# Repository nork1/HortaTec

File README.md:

# HortaTec

Ficheiros com o código utilizado no microcontrolador ESP32-S2, tal como um backup do sistema Home Assistant e os ficheiros do desenvolvimento do PCB no Autodesk EAGLE

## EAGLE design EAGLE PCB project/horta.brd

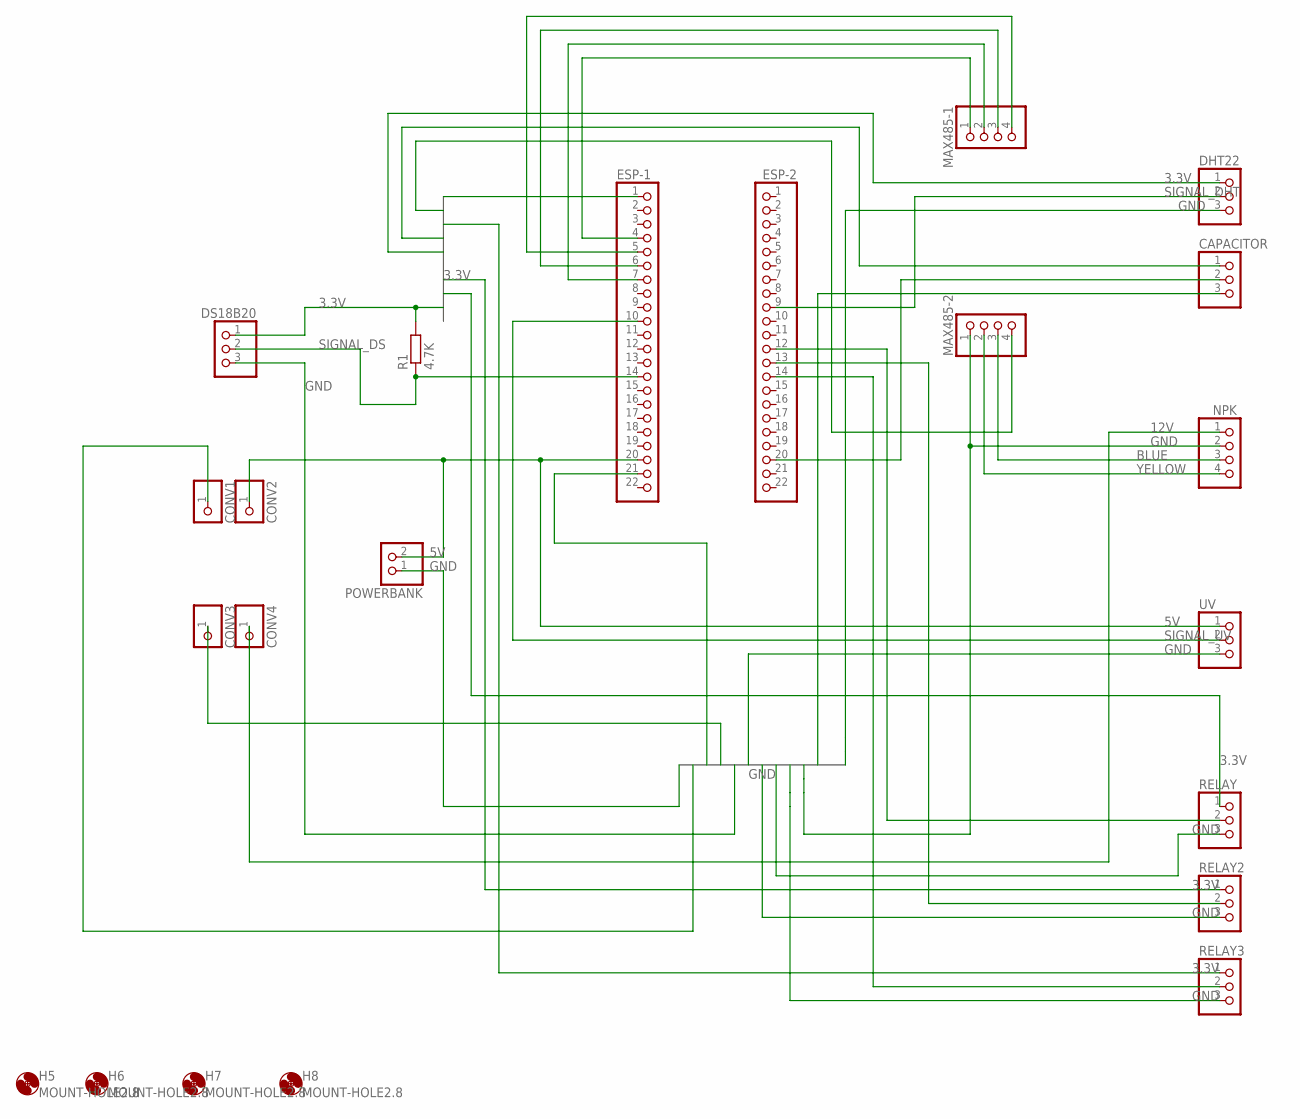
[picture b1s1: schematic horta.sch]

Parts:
CAPACITOR: PINHD-1X3; 1X03
CONV1, CONV2, CONV3, CONV4: PINHD-1X1; 1X01
DHT22: PINHD-1X3; 1X03
DS18B20: PINHD-1X3; 1X03
ESP-1, ESP-2: PINHD-1X22; 1X22
H5, H6, H7, H8: MOUNT-HOLE2.8; 2,8
MAX485-1, MAX485-2: PINHD-1X4; 1X04
NPK: PINHD-1X4; 1X04
POWERBANK: PINHD-1X2; 1X02
R1: 4.7K; 0207/10
RELAY, RELAY2, RELAY3: PINHD-1X3; 1X03
UV: PINHD-1X3; 1X03

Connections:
3.3V: CAPACITOR.1, DHT22.1, DS18B20.1, ESP-1.1, MAX485-2.4, R1.2, RELAY.1, RELAY2.1, RELAY3.1
5V: CONV2.1, ESP-1.20, POWERBANK.2, UV.1
12V: CONV4.1, NPK.1
BLUE: MAX485-2.3, NPK.3
GND: CAPACITOR.3, CONV1.1, CONV3.1, DHT22.3, DS18B20.3, ESP-1.21, MAX485-2.1, NPK.2, POWERBANK.1, RELAY.3, RELAY2.3, RELAY3.3, UV.3
unnamed: ESP-1.4, MAX485-1.1
unnamed: ESP-1.5, MAX485-1.4
unnamed: ESP-1.6, MAX485-1.3
unnamed: ESP-1.7, MAX485-1.2
unnamed: ESP-2.12, RELAY.2
unnamed: CAPACITOR.2, ESP-2.20
unnamed: ESP-2.14, RELAY3.2
unnamed: ESP-2.13, RELAY2.2
SIGNAL_DHT: DHT22.2, ESP-2.9
SIGNAL_DS: DS18B20.2, ESP-1.14, R1.1
SIGNAL_UV: ESP-1.10, UV.2
YELLOW: MAX485-2.2, NPK.4

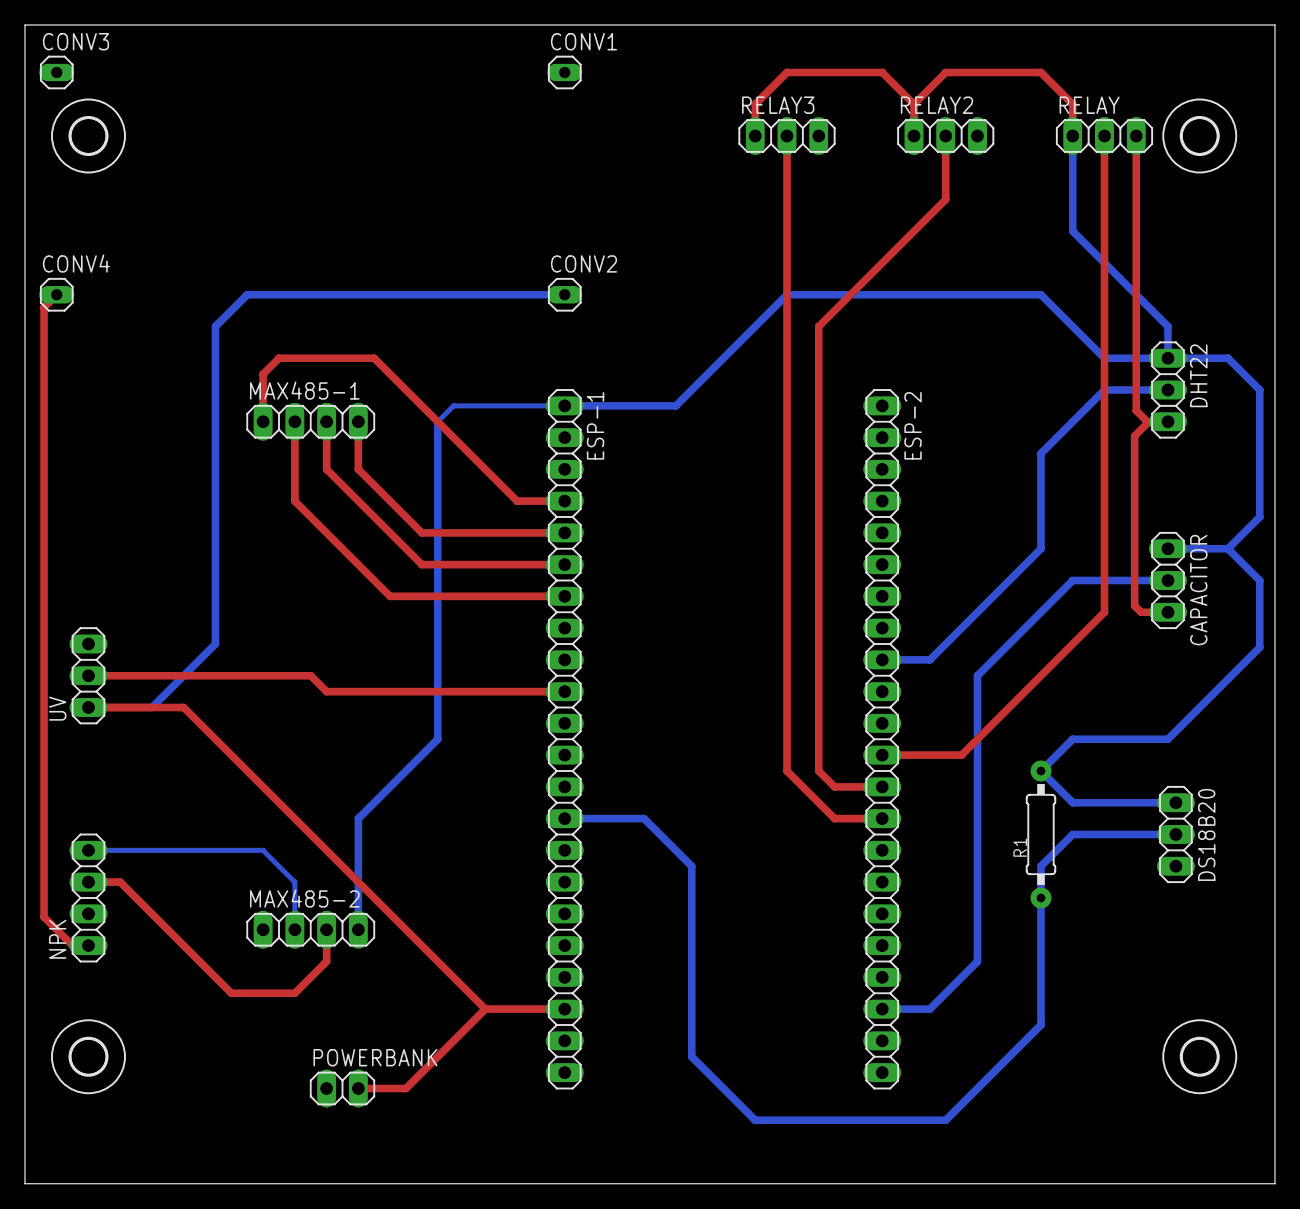
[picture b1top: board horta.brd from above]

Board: 2 copper layers, 100.0 x 92.7 mm, 22 parts (0 on the bottom side), 17 nets.

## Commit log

2022-09-07 Ficheiros Horta
2022-09-08 added backup HA
